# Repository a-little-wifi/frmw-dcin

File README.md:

# Framework laptop DC-in module

This is a Framework laptop module designed to let you use Dell or HP laptop power supplies with a Framework laptop (or any other device that takes 20V USB-PD)

The schematic for this board was made by [Arya](https://github.com/CRImier), I tweaked it a bit and did the board layout.  
It requires an Altmode Friend, also made by Arya, to handle all the communication and control.

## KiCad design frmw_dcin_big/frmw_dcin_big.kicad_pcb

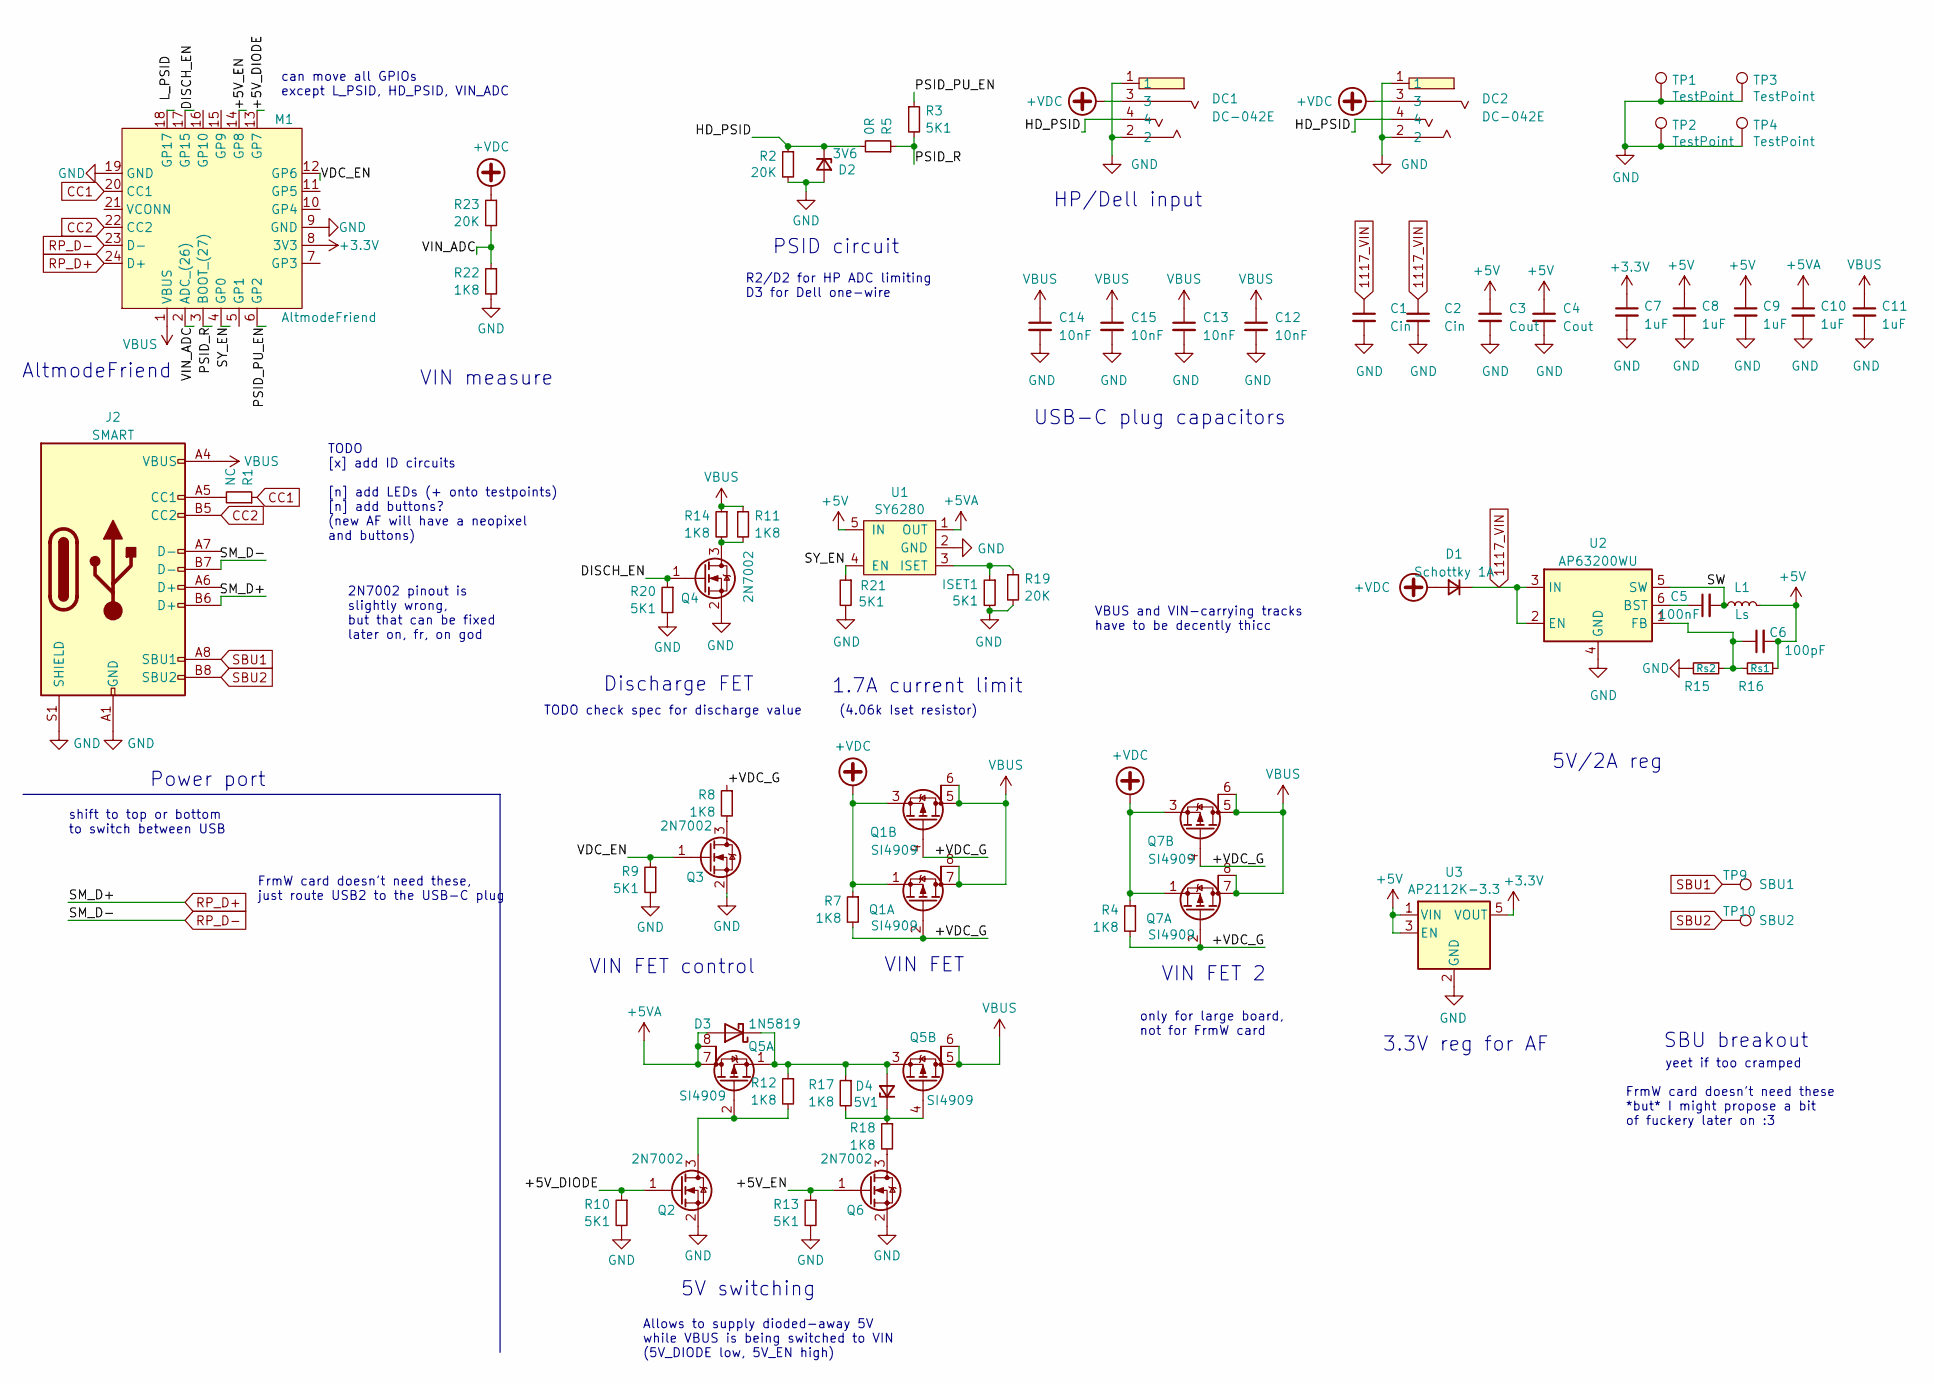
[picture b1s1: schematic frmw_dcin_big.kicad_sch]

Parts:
C1, C2: Cin; C_0805_2012Metric
C3, C4: Cout; C_0805_2012Metric
C5: 100nF; C_0402_1005Metric
C6: 100pF; C_0603_1608Metric
C7, C8, C9, C10, C11: 1uF; C_0402_1005Metric
C12, C13, C14, C15: 10nF; C_0402_1005Metric
D1: Schottky 1A; D_SMA
D2: 3V6; D_0805_2012Metric
D3: 1N5819; D_SMA
D4: 5V1; D_0805_2012Metric
DC1, DC2: DC-042E; DC-IN-TH_DC-042E; LCSC Part C397340
ISET1: 5K1; R_0402_1005Metric
J2: SMART; USB_C_Plug_Molex_105444
L1: Ls; L_Bourns-SRN4018
M1: AltmodeFriend; altmode_friend
Q1, Q5, Q7: SI4909; SO-8_3.9x4.9mm_P1.27mm
Q2, Q3, Q4, Q6: 2N7002; SOT-23
R1: NC; R_0402_1005Metric
R2, R19, R23: 20K; R_0402_1005Metric
R3, R9, R10, R13, R20, R21: 5K1; R_0402_1005Metric
R4, R7, R8, R11, R12, R14, R17, R18, R22: 1K8; R_0402_1005Metric
R5: 0R; R_0402_1005Metric
R15: Rs2; R_0603_1608Metric
R16: Rs1; R_0603_1608Metric
TP1, TP2, TP3, TP4: TestPoint; TestPoint_Pad_1.5x1.5mm
TP9: SBU1; TestPoint_THTPad_D1.0mm_Drill0.5mm
TP10: SBU2; TestPoint_THTPad_D1.0mm_Drill0.5mm
U1: SY6280; SOT-23-5
U2: AP63200WU; TSOT-23-6
U3: AP2112K-3.3; SOT-23-5

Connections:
1117_VIN: C1.1, C2.1, D1.1 (K), U2.2 (EN), U2.3 (IN)
+3.3V: C7.1, M1.8 (3V3), U3.5 (VOUT)
+5V: C3.1, C4.1, C6.2, C8.1, C9.1, L1.2, R16.1, U1.5 (IN), U3.1 (VIN), U3.3 (EN)
+5VA: C10.1, D3.2 (A), Q5.7 (D), Q5.8 (G), U1.1 (OUT)
+VDC: D1.2 (A), DC1.3, DC2.3, Q1.1 (S), Q1.3 (S), Q7.1 (S), Q7.3 (S), R4.1, R7.1, R23.1
/+5V_DIODE: M1.13 (GP7), Q2.1 (G), R10.1
/+5V_EN: M1.14 (GP8), Q6.1 (G), R13.1
/+VDC_G: Q1.2 (G), Q1.4 (G), Q7.2 (G), Q7.4 (G), R4.2, R7.2, R8.1
/DISCH_EN: M1.17 (GP15), Q4.1 (G), R20.1
/HD_PSID: D2.1 (K), DC1.4, DC2.4, R2.1, R5.2
/PSID_PU_EN: M1.6 (GP2), R3.1
/PSID_R: M1.3 (BOOT_(27)), R3.2, R5.1
/SW: C5.2, L1.1, U2.5 (SW)
/SY_EN: M1.4 (GP0), R21.1, U1.4 (EN)
/VDC_EN: M1.12 (GP6), Q3.1 (G), R9.1
/VIN_ADC: M1.2 (ADC_(26)), R22.1, R23.2
CC1: M1.20 (CC1), R1.1
CC2: J2.B5 (CC2), M1.22 (CC2)
GND: C1.2, C2.2, C3.2, C4.2, C7.2, C8.2, C9.2, C10.2, C11.2, C12.2, C13.2, C14.2, C15.2, D2.2 (A), DC1.1, DC1.2, DC2.1, DC2.2, J2.A1 (GND), J2.A12 (GND), J2.B1 (GND), J2.B12 (GND), J2.S1 (SHIELD), M1.9 (GND), M1.19 (GND), Q2.2 (S), Q3.2 (S), Q4.2 (S), Q6.2 (S), R2.2, R9.2, R10.2, R13.2, R15.2, R19.2, R20.2, R21.2, R22.2, TP1.1, TP2.1, TP3.1, TP4.1, U1.2 (GND), U2.4 (GND), U3.2 (GND); also elsewhere on the board
unnamed: D3.1 (K), D4.2 (A), Q5.1 (S), Q5.3 (S), R12.1, R17.1
unnamed: D4.1 (K), Q5.4 (G), R17.2, R18.1
unnamed: J2.A5 (CC1), R1.2
unnamed: Q2.3 (D), Q5.2 (G), R12.2
unnamed: Q3.3 (D), R8.2
unnamed: Q4.3 (D), R11.2, R14.2
unnamed: Q6.3 (D), R18.2
unnamed 26: R19.1, U1.3 (ISET); also elsewhere on the board
unnamed: C5.1, U2.6 (BST)
unnamed: C6.1, R15.1, R16.2, U2.1 (FB)
RP_D+: J2.B6 (D+), M1.24 (D+)
RP_D-: J2.B7 (D-), M1.23 (D-)
SBU1: J2.A8 (SBU1), TP9.1
SBU2: J2.B8 (SBU2), TP10.1
VBUS: C11.1, C12.1, C13.1, C14.1, C15.1, J2.A4 (VBUS), J2.A9 (VBUS), J2.B4 (VBUS), J2.B9 (VBUS), M1.1 (VBUS), Q1.5 (D), Q1.6 (G), Q1.7 (D), Q1.8 (G), Q5.5 (D), Q5.6 (G), Q7.5 (D), Q7.6 (G), Q7.7 (D), Q7.8 (G), R11.1, R14.1

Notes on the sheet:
HP/Dell input
FrmW card doesn't need these *but* I might propose a bit of fuckery later on :3
PSID circuit
3.3V reg for AF
VIN FET control
USB-C plug capacitors
Allows to supply dioded-away 5V while VBUS is being switched to VIN (5V_DIODE low, 5V_EN high)
VIN FET
TODO check spec for discharge value
only for large board, not for FrmW card
can move all GPIOs except L_PSID, HD_PSID, VIN_ADC
shift to top or bottom to switch between USB
5V/2A reg
VBUS and VIN-carrying tracks have to be decently thicc
Power port
AltmodeFriend
VIN FET 2
TODO [x] add ID circuits [n] add LEDs (+ onto testpoints) [n] add buttons? (new AF will have a neopixel and buttons)
(4.06k Iset resistor)
SBU breakout
FrmW card doesn't need these, just route USB2 to the USB-C plug
VIN measure
R2/D2 for HP ADC limiting D3 for Dell one-wire
yeet if too cramped
2N7002 pinout is slightly wrong, but that can be fixed later on, fr, on god
5V switching
1.7A current limit
Discharge FET

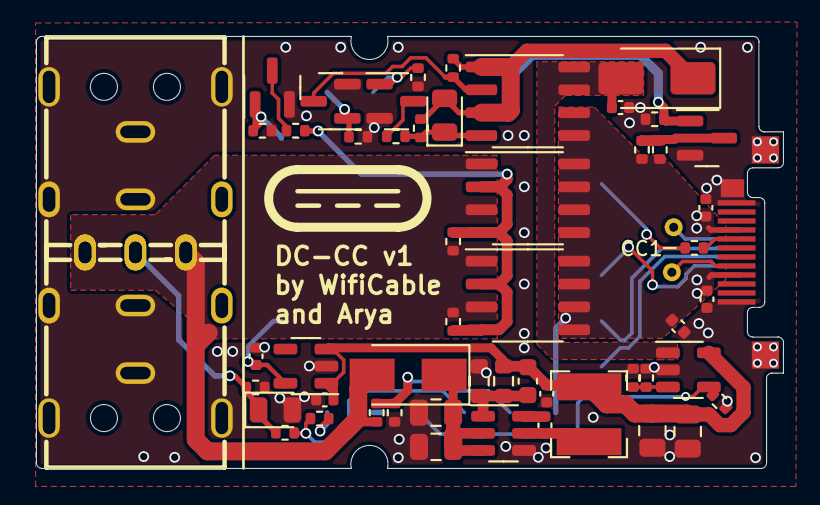
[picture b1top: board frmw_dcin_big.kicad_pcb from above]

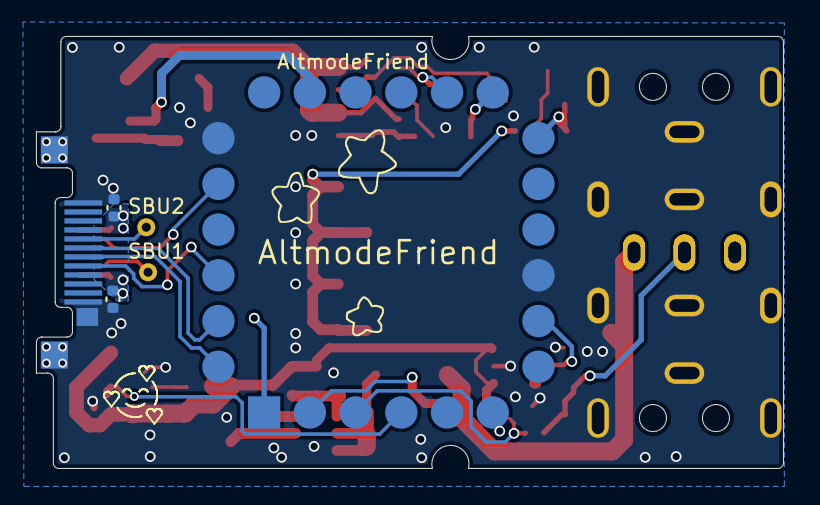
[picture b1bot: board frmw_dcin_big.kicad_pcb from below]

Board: 4 copper layers, 41.5 x 24.0 mm, 63 parts (5 on the bottom side), 34 nets.

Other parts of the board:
R6: 5K1; R_0402_1005Metric

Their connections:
GND: R6.2; also elsewhere on the board
unnamed 26: R6.1; also elsewhere on the board

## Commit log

2024-09-19 Added project files
2024-09-19 Wrote short readme
2025-05-02 design: reviewed. added a proper circuit for HP/Dell center pin detection, did BOM optimizations, recalculated SY6280 resistors, yote via-in-pad, improved tracks and fills, updated USB-C footprint
2025-05-02 Added name and logo
2025-05-02 adjusted logo
2025-05-02 Changed to 4 layers
